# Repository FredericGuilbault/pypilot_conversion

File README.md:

# pypilot_conversion
Details of converting a ST1000/ST2000 tiller pilot into a PyPilot implementation.

## Converting your own. 

#### getting the boards 
most if not any PCB(Printed circuit board) manifacturer works with gerber files, the pypilot_conversion is made of 3 PBC:
 - pypilot_motor
 - pypilot_keyboard
 - pypilot_dome

#### getting the parts
Each board also have a part list of electronics components you will need to solder on the boards. Commonly named BOM(bills of material)

####  Building
Build notes:

- Had to flip one resistor on the keyboard to the front; otherwise it was in the way of a piece of the plastic casing. Also had to tilt the buckdown converter to its side.

- The current measuring is still a bit in progress. The Pololu CS (current sense) pin is supposed to give 'about 20 mV/A plus a 50 mV offset', but setting the servo.current.factor and .offset was not enough; I tweaked motor.ino a bit but don't get a linear reading so far.

Images from the building process: https://photos.app.goo.gl/vQ7VHdccvfHCTUkM7

####  Software
To be used in combination with pypilot_ray replacing pypilot_hat.

https://github.com/marcobergman/pypilot_ray

## Developpement

Work in progress; details follow in due time. Based on a prototype described here https://forum.openmarine.net/showthread.php?tid=1864&pid=9664#pid9664

First findings impression: https://www.youtube.com/watch?v=vbth_teGMJA

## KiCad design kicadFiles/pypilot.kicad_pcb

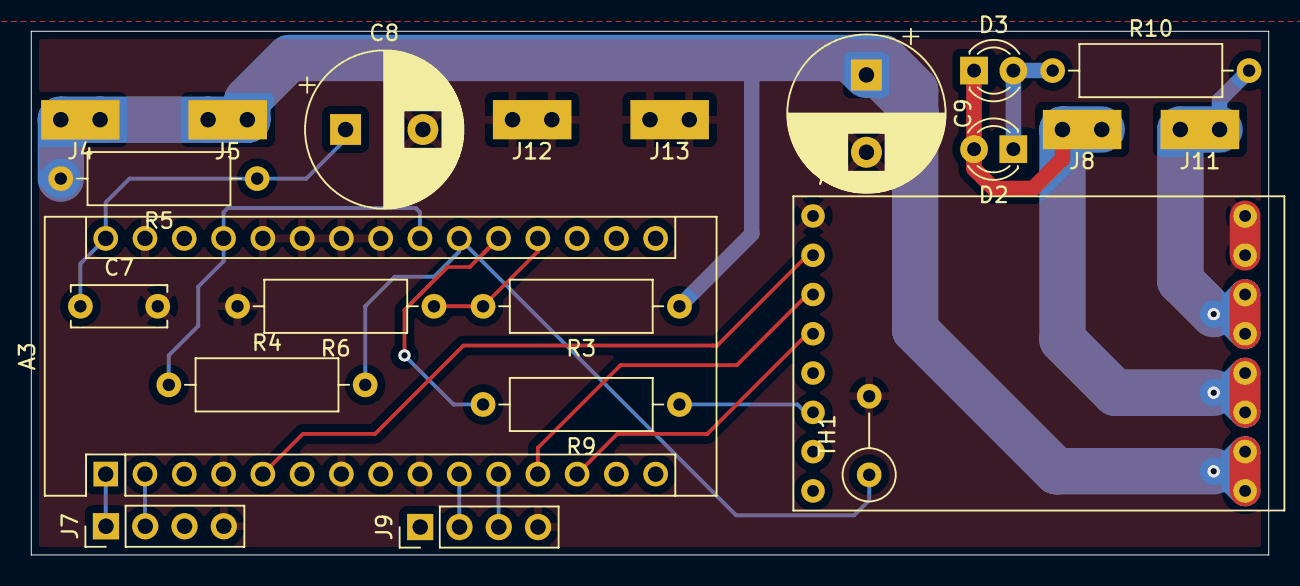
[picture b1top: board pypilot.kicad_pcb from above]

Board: 2 copper layers, 80.0 x 33.9 mm, 22 parts (0 on the bottom side), 18 nets.

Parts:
A3: Arduino_Nano
A4: pololu#2991; Pololu#2991
C7: 0.1uF; C_Disc_D6.0mm_W2.5mm_P5.00mm
C8: 10uF; CP_Radial_D10.0mm_P5.00mm
C9: 470uF; CP_Radial_D10.0mm_P5.00mm
D2: green; LED_D3.0mm
D3: red; LED_D3.0mm
J4, J5: 12V; tab
J7: 1x4; PinHeader_1x04_P2.54mm_Vertical
J8: Motor A; tab
J9: End Stops; PinHeader_1x04_P2.54mm_Vertical
J11: Motor B; tab
J12, J13: GND; tab
R3, R4: 10k; R_Axial_DIN0309_L9.0mm_D3.2mm_P12.70mm_Horizontal
R5: 100; R_Axial_DIN0309_L9.0mm_D3.2mm_P12.70mm_Horizontal
R6, R9, R10: 560; R_Axial_DIN0309_L9.0mm_D3.2mm_P12.70mm_Horizontal
TH1: 10k; R_Axial_DIN0309_L9.0mm_D3.2mm_P5.08mm_Vertical

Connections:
+12V: A4.1, A4.2, C9.1, J4.1, J5.1, R3.1, R5.2
/MOTORA: A4.3, A4.4, D2.2, D3.1, J8.1
/MOTORB: A4.5, A4.6, J11.1, R10.2
DIR: A3.5, A4.10
GND: A3.4, A3.7, A3.9, A3.23, A3.24, A3.25, A3.26, A3.29, A4.7, A4.8, A4.9, C7.2, C8.2, C9.2, J7.4, J9.4, J12.1, J13.1, R6.2, TH1.2
unnamed: A3.1, J7.1
unnamed: A3.2, J7.2
unnamed: A3.10, J9.2
unnamed: A3.11, J9.3
unnamed: A3.19, R3.2, R6.1
unnamed: A3.20, R9.2
unnamed: A3.21, R4.2, TH1.1
unnamed: A3.22, A3.27, R4.1
unnamed: A3.30, C7.1, C8.1, R5.1
unnamed: A4.14, R9.1
unnamed: D2.1, D3.2, R10.1
PWM: A3.12, A4.11
~SLP: A3.13, A4.12

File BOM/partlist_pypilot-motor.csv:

"Id";"Designator";"Package";"Quantity";"Designation";"Supplier and ref";
1;"J11";"tab";1;"Motor B";;;
2;"J8";"tab";1;"Motor A";;;
3;"R4,R3";"R_Axial_DIN0309_L9.0mm_D3.2mm_P12.70mm_Horizontal";2;"10k";;;
4;"TH1";"R_Axial_DIN0309_L9.0mm_D3.2mm_P5.08mm_Vertical";1;"10k";;;
5;"R9,R6,R10";"R_Axial_DIN0309_L9.0mm_D3.2mm_P12.70mm_Horizontal";3;"560";;;
6;"R5";"R_Axial_DIN0309_L9.0mm_D3.2mm_P12.70mm_Horizontal";1;"100";;;
7;"J13,J12";"tab";2;"GND";;;
8;"J9";"PinHeader_1x04_P2.54mm_Vertical";1;"End Stops";;;
9;"J7";"PinHeader_1x04_P2.54mm_Vertical";1;"1x4";;;
10;"J5,J4";"tab";2;"12V";;;
11;"C9";"CP_Radial_D10.0mm_P5.00mm";1;"470uF";;;
12;"C8";"CP_Radial_D10.0mm_P5.00mm";1;"10uF";;;
13;"C7";"C_Disc_D6.0mm_W2.5mm_P5.00mm";1;"0.1uF";;;
14;"A4";"Pololu#2991";1;"pololu#2991";;;
15;"A3";"Arduino_Nano";1;"Arduino_Nano";;;
16;"D2";"LED_D3.0mm";1;"green";;;
17;"D3";"LED_D3.0mm";1;"red";;;

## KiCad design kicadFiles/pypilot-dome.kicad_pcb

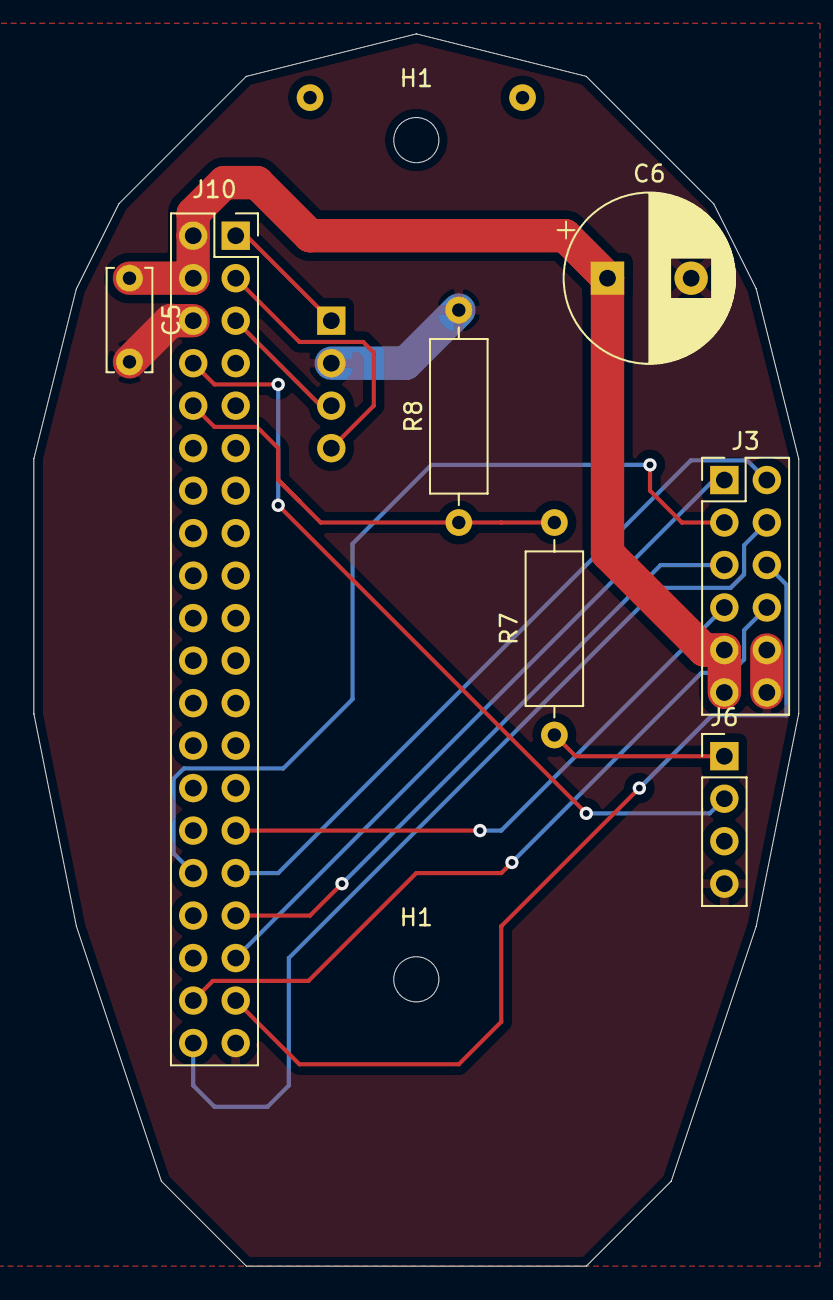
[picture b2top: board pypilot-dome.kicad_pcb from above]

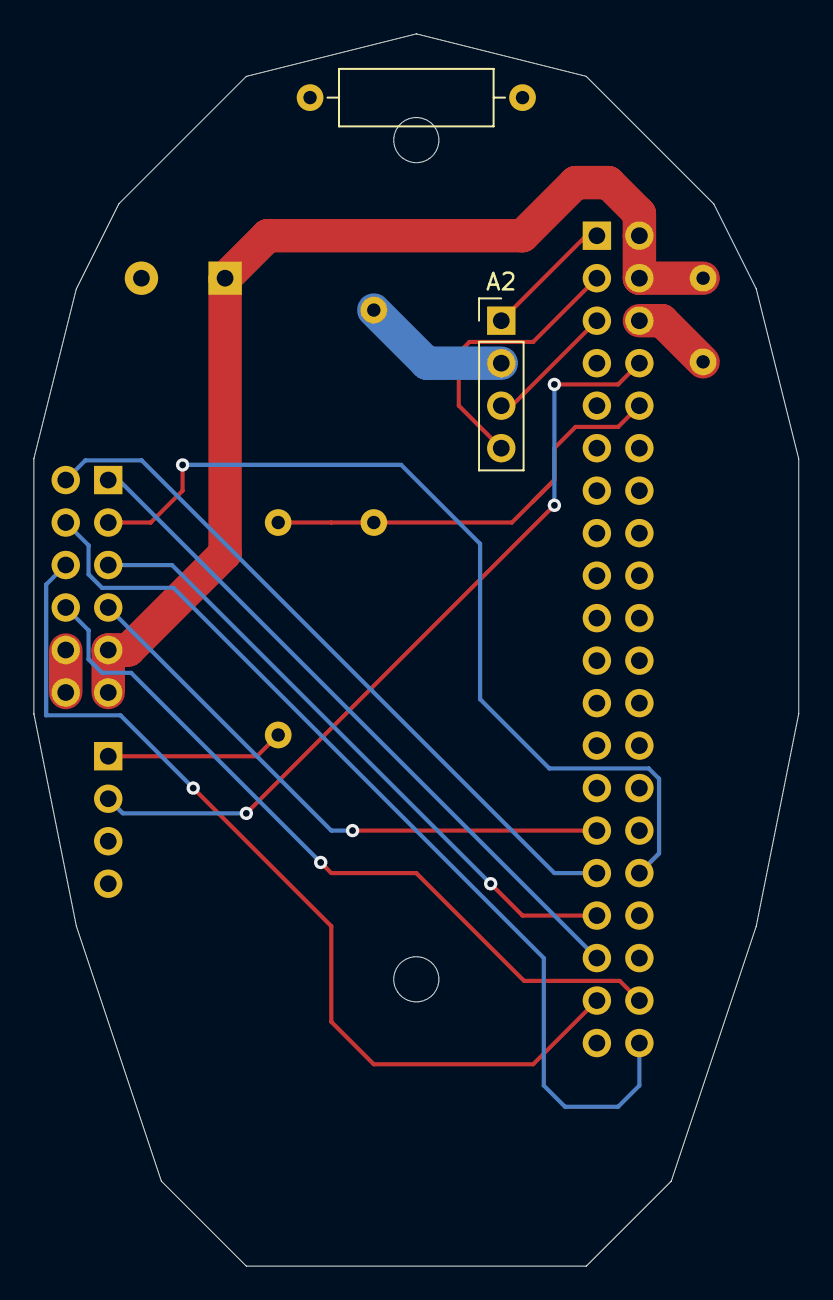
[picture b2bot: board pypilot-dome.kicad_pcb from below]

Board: 2 copper layers, 45.7 x 73.7 mm, 11 parts (2 on the bottom side), 16 nets.

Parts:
A2: MPU-9255; PinHeader_1x04_P2.54mm_Vertical
C5: 0.1uF; C_Disc_D6.0mm_W2.5mm_P5.00mm
C6: 10uF; CP_Radial_D10.0mm_P5.00mm
H1, H1#2: MountingHole; MountingHole_2.7mm
J3: 2x6; PinHeader_2x06_P2.54mm_Vertical
J6: 1x4; PinHeader_1x04_P2.54mm_Vertical
J10: PiZero W; PinSocket_2x20_P2.54mm_Vertical
R7, R8: R; R_Axial_DIN0309_L9.0mm_D3.2mm_P12.70mm_Horizontal
R10: 560; R_Axial_DIN0309_L9.0mm_D3.2mm_P12.70mm_Horizontal

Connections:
+1: J3.5, J10.33
+5V: C5.1, C6.1, J3.9, J3.11, J10.2, J10.4
+10: J3.3, J10.32
-1: J3.7, J10.29
-10: J3.2, J10.31
AUTO: J3.6, J10.37
Buzzer: J3.8, J10.38
GND: A2.2, C5.2, C6.2, J3.10, J3.12, J6.4, J10.6, J10.39, R8.2
LED: J3.1, J10.35
unnamed: A2.1, J10.1
unnamed: A2.3, J10.5
unnamed: A2.4, J10.3
unnamed: J6.1, R7.1
unnamed: J6.2, J10.8
unnamed: J10.10, R7.2, R8.1
StandBy: J3.4, J10.40

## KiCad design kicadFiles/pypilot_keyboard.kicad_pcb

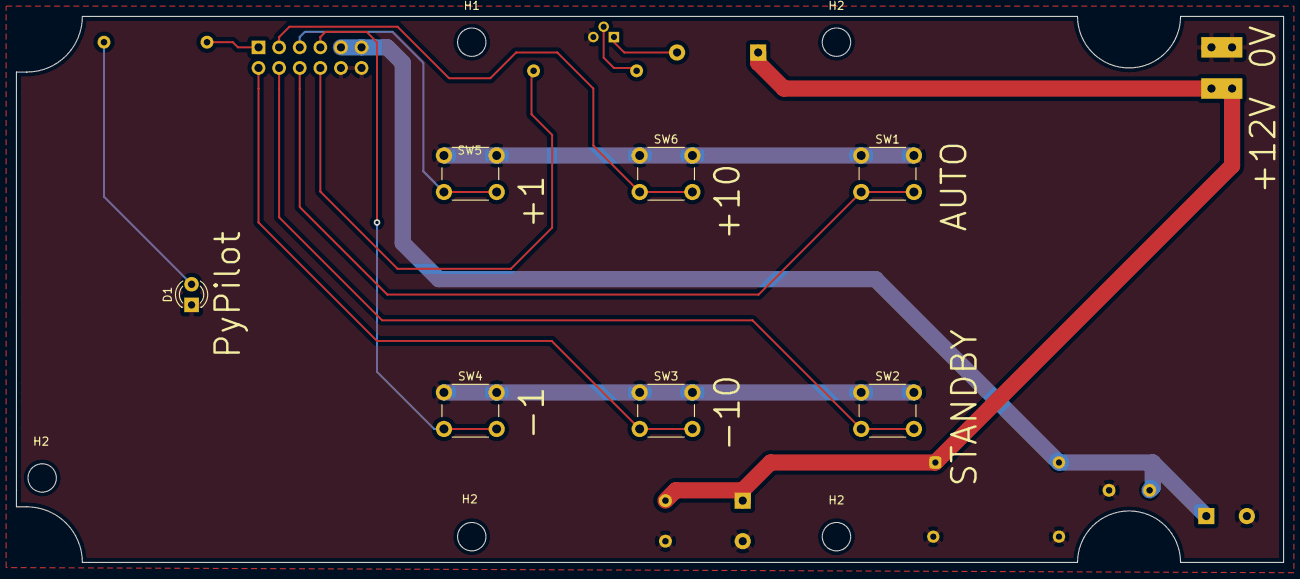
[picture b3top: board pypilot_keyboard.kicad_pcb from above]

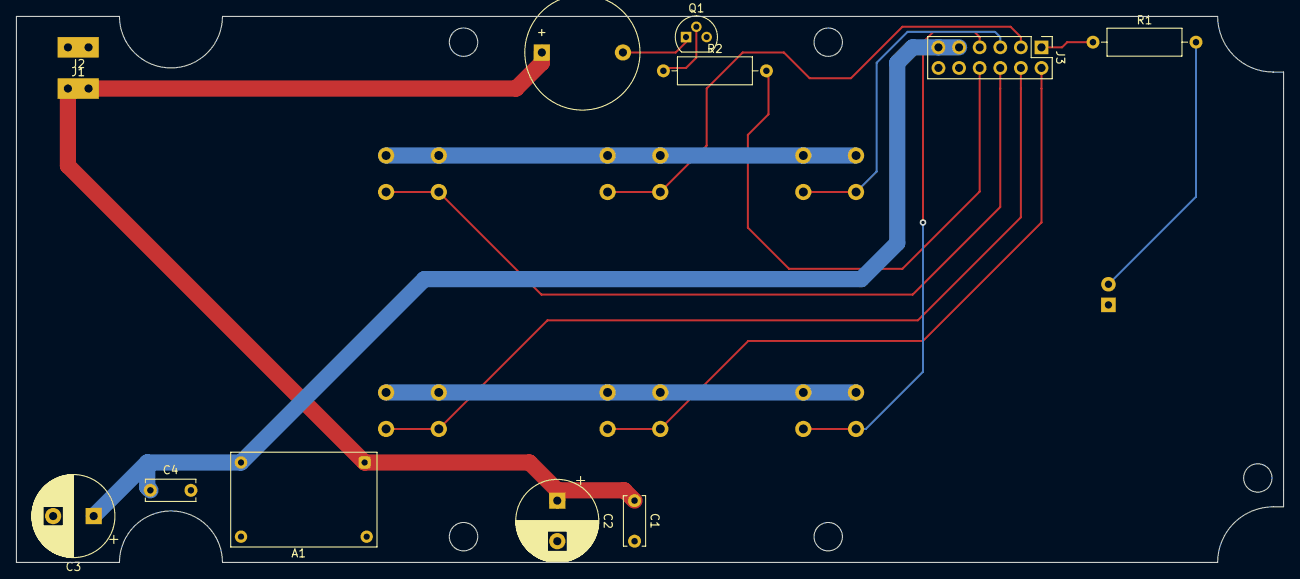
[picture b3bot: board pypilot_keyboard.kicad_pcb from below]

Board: 2 copper layers, 156.2 x 67.3 mm, 24 parts (12 on the bottom side), 14 nets.

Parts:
A1: MH-MINI-360
BZ1: Buzzer; Buzzer_D14mm_H7mm_P10mm
C1, C4: 0.1uF; C_Disc_D6.0mm_W2.5mm_P5.00mm
C2, C3: 10uF; CP_Radial_D10.0mm_P5.00mm
D1: LED; LED_D3.0mm
H1, H2, H2#2, H2#3, H2#4: MountingHole; MountingHole_3.5mm
J1: Power +12V; tab
J2: Power 0V; tab
J3: 2x6; PinHeader_2x06_P2.54mm_Vertical
Q1: BC547; TO-92
R1: 1k2; R_Axial_DIN0309_L9.0mm_D3.2mm_P12.70mm_Horizontal
R2: R; R_Axial_DIN0309_L9.0mm_D3.2mm_P12.70mm_Horizontal
SW1: Auto; SW_PUSH_6mm
SW2: StdBy; SW_PUSH_6mm
SW3: -10; SW_PUSH_6mm
SW4: -1; SW_PUSH_6mm
SW5: +1; SW_PUSH_6mm
SW6: +10; SW_PUSH_6mm

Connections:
+1: J3.5, SW5.2
+5V: A1.2, C3.1, C4.1, J3.9, J3.11
+10: J3.3, SW6.2
+12V: A1.1, BZ1.1, C1.1, C2.1, J1.1
-1: J3.7, SW4.2
-10: J3.2, SW3.2
AUTO: J3.6, SW1.2
Buzzer: J3.8, R2.2
GND: A1.3, A1.4, C1.2, C2.2, C3.2, C4.2, D1.1, J2.1, J3.10, J3.12, Q1.3, SW1.1, SW2.1, SW3.1, SW4.1, SW5.1, SW6.1
LED: J3.1, R1.1
unnamed: BZ1.2, Q1.1
unnamed: D1.2, R1.2
unnamed: Q1.2, R2.1
StandBy: J3.4, SW2.2

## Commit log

2024-02-27 remove zipped content, restructure files location.
2024-02-28 Update documentation to reflect new file structure
2024-03-08 Fix Problem where motor wrongly report 170°C due to error in wiring
2024-03-09 2nd Fix Problem where motor wrongly report 170°C due to error in wiring
2024-03-12 Update gerber files
2024-03-15 add details to the BOM
